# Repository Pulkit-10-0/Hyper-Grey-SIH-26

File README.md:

<h1 align="center">SeaNergy · HyperGrey</h1>
<p align="center"><strong>Sonar that reads the water before it sends the ping.</strong></p>
<p align="center">A low-power, adaptive software-defined sonar transmitter payload for autonomous underwater vehicles.</p>

<p align="center">
  <a href="https://www.hypergrey.in/">Project website</a> ·
  <a href="https://www.youtube.com/playlist?list=PLfZXQHCNRlPQ">Demo playlist</a> ·
  <a href="04-software/releases/SeaNergy-2.2.0___android.apk">Android APK</a> ·
  <a href="07-documentation/research-paper/SeaNergy_Adaptive_Sonar_Research_Paper.pdf">Research paper</a> ·
  <a href="https://www.kaggle.com/code/prakhar1803/adaptive-sonar-waveform-selection">Kaggle notebook</a>
</p>

*The two-DSO bench setup: two digital oscilloscopes, waveform dashboards, controller electronics, probe vessels, and the printed payload housing. September 2026 prototype session.*

SeaNergy is **HyperGrey's Smart India Hackathon 2026** response to **SIH26058**, from the **Ministry of Earth Sciences / National Institute of Ocean Technology**. The problem asks for a low-power, real-time adaptive software-defined sonar transmitter payload for AUVs. Our work connects underwater acoustics, constrained waveform selection, embedded signal generation, analog electronics, mechanical fabrication, and an offline operator console.

The central question is practical: **what pulse should an AUV send next, given the water, the mission, and its energy budget?** SeaNergy makes that decision inspectable—from environmental inputs and propagation assumptions to frequency, bandwidth, pulse duration, waveform, and detection estimates.

## Prototype gallery

A closer look at the physical build, hands-on tuning, and instrumented bench work. Click any photograph to open the original.

| Controller and local displays | Hands-on bench tuning |
|:---:|:---:|
|  |  |
| Four OLEDs, manual controls, sensor wiring, and the breadboard transducer stage. | Adjusting the prototype controls while observing the electrical signals. |

| Two-DSO waveform checks | Burst transmission on the bench |
|:---:|:---:|
|  |  |
| Two oscilloscopes used side by side to inspect electrical waveforms. | Repeated carrier packets separated by quiet intervals. |

### App screens

| Console | Sonar view | Diagnostics |
|:---:|:---:|:---:|
|  |  |  |

*Simulation-mode app screenshots. More environment, waveform, and spectrum views appear in [Operator software](#operator-software). Click a screenshot for its full-resolution view.*

### Graphs dashboard

*September 2026 development dashboard combining serial input readouts with computed waveform, spectral, pulse-compression, propagation, and solver plots. Click to inspect the full-resolution dashboard.*

## Start with the evidence

| Review route | What to open |
|---|---|
| **See the prototype** | [Hardware demo with DSO](https://www.youtube.com/watch?v=S5sL9P1SnnM), [changing water conditions](https://www.youtube.com/watch?v=R3WoJ25fv1Y), and [prototype photographs](08-media/photos/) |
| **Try the interface** | [Android v2.2.0 APK](04-software/releases/SeaNergy-2.2.0___android.apk), [app demo](https://www.youtube.com/watch?v=PedR7m0j_bs), and [software guide](04-software/README.md) |
| **Inspect the engineering** | [Hardware design](01-hardware/README.md), [board verification](01-hardware/verification-summary.md), and [current TX/RX firmware](02-firmware/README.md) |
| **Check the reasoning** | [21-page project research paper](07-documentation/research-paper/SeaNergy_Adaptive_Sonar_Research_Paper.pdf), [literature library](03-research/README.md), and [reproducible modelling package](05-models/) |
| **Review the submission** | [Compliance material](00-submission/compliance-matrix/) and [demo procedure](00-submission/demo-script/demo-script.md) |

**Contents:** [Photo gallery](#prototype-gallery) · [App screens](#app-screens) · [Graphs dashboard](#graphs-dashboard) · [Problem and approach](#problem-and-approach) · [Architecture](#architecture) · [Prototype and hardware](#prototype-and-hardware) · [Firmware](#firmware) · [Research and results](#research-and-results) · [Operator software](#operator-software) · [Verification](#verification-results) · [Reproduce](#reproduce-the-work) · [Team](#team-and-ownership)

## Problem and approach

An AUV carries a finite energy store into water whose acoustic properties change. Higher frequencies can provide finer detail, but propagation loss rises with frequency. A longer pulse carries more energy, but an unmodulated pulse also broadens the return in time. Turbidity introduces further loss and uncertainty; temperature, salinity, depth, and pH affect the propagation model. A fixed waveform therefore commits to one compromise across changing conditions.

SeaNergy explores a transmitter that can adjust that compromise deliberately:

1. **Read the environment.** Use measured inputs where calibrated sensing is available, or explicit simulation inputs during model development.
2. **Estimate propagation.** Calculate sound speed, absorption, scattering loss, and the active-sonar link budget under stated assumptions.
3. **Choose a feasible pulse.** Search a bounded candidate set for useful bandwidth while respecting detection margin and energy constraints.
4. **Generate the waveform.** Prepare a digital pulse, apply its envelope, and let the output peripheral clock the samples.
5. **Inspect the result.** Expose waveform, spectrum, diagnostics, and decision inputs to the operator. The software model also studies echo correlation and feedback.

The intended applications include AUV inspection, survey, and obstacle sensing. SeaNergy brings these ideas into a **bench prototype and engineering development platform**, supported by hardware demonstrations, an operator console, and reproducible research.

## Architecture

The system design brings together environmental sensing, acoustic transmit/receive electronics, embedded processing, and the SeaNergy operator app.

*System design overview showing environmental sensing, acoustic signal paths, embedded processing, mobile connectivity, and session export. Component choices and bench wiring are detailed in the [hardware](01-hardware/README.md) and [TX/RX firmware](02-firmware/README.md) guides. Click the diagram to view it at full resolution.*

| Workstream | Implementation | Delivered artifacts |
|---|---|---|
| **Physical prototype** | Sensor/control electronics, displays, nominal 40 kHz electrical carrier and bursts, printed payload housing | Bench photographs, oscilloscope captures, and demonstration videos |
| **PCB design** | AUV V3 Compact Rev B, 100 × 100 mm, two copper layers, 91 footprints | Checked KiCad project, schematics, BOM, and manufacturing package |
| **Embedded software** | Independent TX synthesis/DMA and RX capture/viewer projects | Source, host waveform tests, cross-build records, and wiring guides |
| **Decision research** | Reproducible 100–500 kHz numerical study with 20,000 generated rows | Dataset, notebook, evaluation metrics, and figures |
| **Operator console** | Offline simulation and telemetry adapters; Android release and iOS source | Android APKs, application source, interface demos, and connection specifications |

## Prototype and hardware

### From bench assembly to a payload form

| Bench integration | Printed payload housing |
|:---:|:---:|
|  |  |
| Prototype electronics, sensor vessels, instrument checks, and operator software in one development setup. | Fabricated housing showing the intended payload form and electronics packaging work. |

| Early prototype integration | Housing fabrication |
|:---:|:---:|
|  |  |
| Sensor connections, local displays, controller electronics, and the breadboard stage during early integration. | The physical printed part and support structure during fabrication. |

The bench assembly made the project tangible: real controllers, analog interfaces, sensor inputs, OLED readouts, transmit/receive elements, and instrumented output. Mechanical work progressed through CAD and 3D printing to physical parts. The [fabrication photo](08-media/readme/SeaNergy-payload-fabrication.jpeg), [fabrication time-lapse](https://www.youtube.com/watch?v=OgWcE8eJ3iM), [STL](01-hardware/enclosure/cad/hyper-grey-v1.stl), and [enclosure documentation](01-hardware/enclosure/) preserve that process.

### Electrical observations

| Nominal 40 kHz carrier | Gated carrier packets |
|:---:|:---:|
|  |  |
| Instrument display: **39.99 kHz**, **25.00 μs**, **3.56 V peak-to-peak**. | Carrier cycles grouped into bursts with gaps between transmissions. |

These September 2026 captures document the prototype's electrical carrier and burst behaviour. The carrier display records **39.99 kHz**, **25.00 μs**, and **3.56 V peak-to-peak**; the burst view shows grouped carrier packets and quiet intervals.

<details>
<summary>Additional oscilloscope observations from the supplied bench session</summary>

| Periodic oscillation | Analog trace with switching transients |
|:---:|:---:|
|  |  |

Additional electrical observations from the September bench session show periodic oscillation, decay, and switching transients. Capture provenance is indexed in the [media guide](08-media/readme/README.md).

</details>

### AUV V3 Compact Rev B PCB

*PCB design render of the checked Rev B manufacturing release.*

The compact interconnect PCB provides wired connections for an **ESP32-S3 main/transmit controller** and a **separate ESP32 receiver**. Controllers and other external modules connect through labelled solder pads and require separate mounting; the 100 × 100 mm dimension describes the interconnect PCB. Its interfaces include two ADS1115 ADCs, DS18B20 temperature sensing, TDS and turbidity channels, four OLED displays, a MAX98357A audio path, and nominal 40 kHz transmit/receive connections. The receive section includes a biased analog gain stage. Main and receive electronics have separate 3.3 V rails with a common ground.

The design spans seven schematic sheets. The [saved verification report](01-hardware/kicad/verification/final-verification.json) records 91 footprints, 483 track segments, six vias, and two ground zones, with **zero ERC violations, zero DRC violations, zero unconnected items, and zero schematic/PCB parity issues**. The saved report provides the design-verification record for this release.

**Inspect or manufacture:** [schematic PDF](01-hardware/schematics/schematic.pdf) · [assembly PDF](01-hardware/kicad/previews/Assembly.pdf) · [Gerber ZIP](01-hardware/pcb/gerbers/AUV_V3_RevB_Compact_Gerbers.zip) · [BOM](01-hardware/bom/) · [release checksums](01-hardware/release-sha256.json) · [wiring and design notes](01-hardware/README.md).

## Firmware

The current firmware uses two independently buildable PlatformIO projects. The implementation separates waveform preparation from peripheral playback so the CPU does not have to write every sample at transmission time.

| Component | Implemented behaviour |
|---|---|
| **ESP32-S3 TX** | Fixed-point carrier phase accumulator and sine lookup table; cached pulse synthesis; complete stereo-buffer preload into I2S DMA; hardware-clocked playback |
| **Waveform modes** | Linear frequency modulation, geometric/logarithmic sweep, and Barker-13 BPSK; Barker uses a fixed midpoint carrier with 13 phase-coded chips |
| **PCM envelopes** | Hann, Blackman, and endpoint-tapered Hamming; mode/window selection and actual sample preview on the displays |
| **Burst scheduling** | GPTimer scheduling and separate GPIO16 PWM gating; no busy-wait sample loop |
| **Control and faults** | Disarmed boot, explicit ARM/STOP, stale-input detection, control heartbeat, playback deadline, missed-period and late-gate faults |
| **ESP32 RX** | GPIO34 ADC capture through I2S DMA, ASCII serial frames, and a Python live waveform/Hann-FFT viewer |

### Output profiles

- **Existing MAX98357A profile:** 48 ksample/s PCM playback with **1–8 kHz** waveform settings. A separate GPIO16 output provides **38–42 kHz rectangular PWM bursts**. The chirp arrays and PCM envelopes apply to I2S, not to that PWM output.
- **Optional PCM5102A profile:** 384 ksample/s PCM for a **38–42 kHz** bench configuration, with documented DAC wiring and a buffered line-level frontend for a suitable power driver.
- **Research profile:** a separate **100–500 kHz numerical study** explores waveform selection and propagation trade-offs.

Five physical potentiometers provide bounded frequency, bandwidth, duration, and amplitude mappings, with sensor voltages and temperature reported separately. Each firmware project includes wiring and bench procedures; [compatibility notes](02-firmware/README.md) map the current five-control TX and earlier three-control board companion.

TX and RX operate as independent bench projects: TX prepares and transmits bursts, while RX captures ADC frames for waveform and FFT inspection. The [earlier ESP-IDF parallel-DAC implementation](02-firmware/legacy/esp-idf-payload/) is preserved as a documented development stage.

**Read the implementation:** [TX guide](02-firmware/tx/README.md) · [TX hardware profiles and bench procedure](02-firmware/tx/HARDWARE.md) · [RX project](02-firmware/rx/) · [architecture](02-firmware/docs/architecture.md).

## Research and results

### Literature that shaped the design

The [research library](03-research/README.md) contains **132 reference PDFs across 15 topic areas**, with topic indexes connecting papers to design decisions. It covers sound speed, absorption, sediment scattering, sonar detection, chirp design, matched filtering, windows and sidelobes, phase codes, cognitive sonar, DDS, transducers, AUV integration, embedded power, and machine learning.

The foundations include Mackenzie's sound-speed relation, Thorp and Francois–Garrison absorption models, active-sonar link budgets, Harris's window analysis, and Barker codes. The [21-page project manuscript](07-documentation/research-paper/SeaNergy_Adaptive_Sonar_Research_Paper.pdf), **“Physics-Constrained Adaptive Sonar Waveform Selection and Low-Power Transmit Architecture for Autonomous Underwater Vehicles,”** brings the modelling, architecture, experiments, and engineering analysis together, with generated studies, team-reported observations, and engineering projections identified within it.

### The decision engine

Each solve evaluates **468 candidates: 13 centre frequencies × 6 bandwidth fractions × 6 pulse durations**. The solver checks the modelled detection margin and energy budget, prioritizes useful feasible bandwidth, and uses energy to distinguish equivalent choices. It includes explicit fallback behaviour when the requested margin cannot be achieved.

The main relationships make the trade-offs visible:

| Relationship | Design implication |
|---|---|
| Range resolution: **ΔR ≈ c / (2B)** | Wider effective bandwidth can separate closer reflectors after compression |
| Pulse-compression gain: **≈ 10 log₁₀(BT)** | A swept pulse can combine pulse energy with a narrower compressed response |
| Two-way propagation loss | A return must survive both outward and return travel; frequency and range matter together |
| Windowing | Lower sidelobes trade against main-lobe width and usable pulse energy |

The notebook uses **Mackenzie + Thorp + parameterized scattering**. The current app implements **Mackenzie + Francois–Garrison**, including depth and pH effects. Each implementation documents its modelling assumptions and calculated resolution.

*Generated numerical study in the 100–500 kHz band, showing selected frequency and calculated resolution under the solver's propagation-loss model.*

### Reproducible dataset

The [dataset](05-models/dataset/adaptive_sonar_waveform_selection.csv) contains **20,000 generated rows and 27 columns**, with seed **20260829**. Its sampling deliberately combines broad coverage with difficult cases:

| Stratum | Rows | Purpose |
|---|---:|---|
| Sweep | 8,000 | Controlled exploration of environmental changes |
| Fill | 5,000 | Broader coverage between selected conditions |
| Scenario | 4,000 | Mission-style combinations of conditions |
| Adversarial | 3,000 | Stress cases outside the requested feasible operating margin |

The generated transmit-side dataset covers **15,399 feasible decisions and 4,601 cases outside the requested margin** under the requested margin, exercising both normal selection and fallback behaviour.

### What the model comparison taught us

We trained three histogram gradient-boosting regressors to imitate the solver's centre frequency, bandwidth, and duration decisions. The routine split contains **12,750 training rows and 4,250 test rows**, with a separate **3,000-row stress set**. The stored [evaluation metrics](05-models/evaluation/metrics.json) report:

| Target | Constant mean baseline MAE | Surrogate MAE | Reduction |
|---|---:|---:|---:|
| Centre frequency | 69.57 kHz | 3.58 kHz | 94.8% |
| Bandwidth | 61.30 kHz | 4.00 kHz | 93.5% |
| Pulse duration | 2.404 ms | 1.666 ms | 30.7% |

The comparison supports retaining the bounded solver as the decision reference. The evaluation uses pre-decision environmental and reference-band features following a leakage audit. On the recorded **development-host benchmark**, the precomputed solver's median was **40.3 μs**, compared with **7.45 ms** for single-row Python surrogate inference.

A separate **synthetic residual-correction study** evaluates learning propagation-model error. Its gradient-boosting correction achieved **0.729 dB MAE**, compared with **1.005 dB** for a linear turbidity model and **1.963 dB** for a constant correction.

**Explore:** [notebook and figures](05-models/notebook/) · [evaluation methods and results](05-models/evaluation/) · [Kaggle version](https://www.kaggle.com/code/prakhar1803/adaptive-sonar-waveform-selection) · [dataset checks](05-models/qa.py).

## Operator software

The console turns the physics and signal-processing work into an interface that can be demonstrated without a network connection. It runs the numerical work on the device and labels **Simulation** and **Telemetry** modes explicitly.

| Environment | Waveform | Spectrum |
|:---:|:---:|:---:|
|  |  |  |

*App screenshots in simulation mode. Frequencies, compression, echo, resolution, and power values in this mode are numerical outputs.*

The current source provides **11 tabs plus a Scenario screen**, with individual ping detail. Together they cover the console, sonar PPI, waveform, spectrum, echo/correlation, environment, mission, power, diagnostics, logs, settings, and scenarios.

| Capability | Implementation |
|---|---|
| **Environmental reasoning** | Temperature, salinity, turbidity, depth, and pH inputs; sound-speed and absorption breakdown |
| **Waveform inspection** | CW, LFM, geometric sweeps, Barker-13; rectangular, Hann, Hamming, and Blackman windows |
| **Signal processing** | FFT, spectrogram, transmit replica, modelled echo, and matched-filter analysis in simulation |
| **Operator workflow** | Mission parameters, diagnostics, last 200 ping records in memory, and local CSV export |
| **Android links** | Native USB CDC-ACM/CP210x and BLE adapters; Wi-Fi WebSocket with HTTP fallback |
| **iOS source** | Shared application source, native Xcode project, and Wi-Fi connection path |

The console includes a documented telemetry contract for environmental readings and pulse settings. Its simulation engine, connection adapters, and the standalone RX waveform viewer are described in the [software guide](04-software/README.md) and [firmware architecture](02-firmware/docs/architecture.md).

**Stack:** React Native **0.86.2**, Expo **57**, React **19**, TypeScript, Skia charts, and a Kotlin Android connection module. The [static project website](04-software/website/) uses HTML, CSS, and JavaScript and can run locally without a backend.

**Install or inspect:** [universal Android APK](04-software/releases/SeaNergy-2.2.0___android.apk) · [smaller architecture-specific APKs](04-software/releases/) · [release record](04-software/releases/BUILDS.md) · [Android source](04-software/mobile-android/) · [iOS source](04-software/mobile-ios/) · [software guide](04-software/README.md).

## Demonstration library

The [Hyper Grey SIH 2026 (SeaNergy) playlist](https://www.youtube.com/playlist?list=PLfZXQHCNRlPQ) contains six videos, verified on **16 October 2026**:

| Video | Duration |
|---|---:|
| [1.1 Hardware Demo (with DSO)](https://www.youtube.com/watch?v=S5sL9P1SnnM) | 1:17 |
| [1.2 Hardware Demo ( Changing Water Conditions )](https://www.youtube.com/watch?v=R3WoJ25fv1Y) | 1:54 |
| [2.1 android app demo](https://www.youtube.com/watch?v=PedR7m0j_bs) | 4:43 |
| [3.1 Hardware parts description](https://www.youtube.com/watch?v=1TF7gd7LjTs) | 3:51 |
| [3.2 Hardware Graphs: Overview and Approach](https://www.youtube.com/watch?v=NZ1CEJT-cyo) | 3:23 |
| [Custom Payload Fabrication Time-Lapse](https://www.youtube.com/watch?v=OgWcE8eJ3iM) | 0:09 |

Additional material: [Google Drive photo collection](https://drive.google.com/drive/folders/15Eb-qjRcj5WRZOpzTAzsjD7BbMPWwIrb?usp=sharing) · [repository photo archive](08-media/photos/) · [media provenance and captions](08-media/readme/README.md).

## Verification results

Completed checks cover PCB consistency, embedded waveform generation, application behaviour, and reproducible modelling.

| Evidence | Recorded result | What it establishes |
|---|---|---|
| **Bench photographs and scope captures** | Physical assembly, displayed nominal 40 kHz carrier, and burst packets | Earlier prototype construction and electrical observations |
| **Rev B KiCad checks** | ERC/DRC/unconnected/parity all zero | Design consistency and routing checks for the saved board revision |
| **Current TX host waveform tests** | **409,765 checks passed**, strict C++17 build with undefined-behaviour sanitizer | Analytic waveform agreement, window/mode combinations, bounds, endpoints, amplitude and stereo behaviour |
| **Current TX cross-build record** | Existing, headless, and PCM5102A profiles passed on 16 October 2026 | Source compilation across the three pinned hardware profiles |
| **Android release record** | **106 core assertions and 33 render tests**, with TypeScript checks recorded for v2.2.0 | Core logic, rendered screens, and release-time type checks |
| **Research artifacts** | Generated dataset, notebook, metrics, figures, and QA script | Reproducible numerical work under the documented models |
| **Validation dossier** | Test plans, procedures, and labelled engineering projections | Requirements traceability, acceptance criteria, and test documentation |

The [validation folder](06-validation/), [firmware measurement notes](02-firmware/measurements/README.md), [board report](01-hardware/verification-summary.md), and [software build record](04-software/releases/BUILDS.md) provide procedures, conditions, and supporting records.

## Reproduce the work

### Firmware builds

Install PlatformIO, then run these commands from the repository root. The optional DAC profile compiles independently but requires its documented hardware before use.

```sh
pio run -d 02-firmware/tx -e esp32s3_existing
pio run -d 02-firmware/tx -e esp32s3_headless
pio run -d 02-firmware/tx -e esp32s3_pcm5102a
pio run -d 02-firmware/rx -e esp32dev
```

Run the portable waveform checks with a C++17 compiler:

```sh
cd 02-firmware/tx
c++ -std=c++17 -O1 -Wall -Wextra -Werror -pedantic \
  -fsanitize=undefined -Iinclude src/waveform.cpp tests/waveform_test.cpp \
  -o /tmp/seanergy-waveform-test
/tmp/seanergy-waveform-test
```

For wiring, serial commands, fault handling, and bench measurements, start with the [firmware guide](02-firmware/README.md).

### Research notebook and evaluation

Use **Python 3.12** in a virtual environment. Starting at the repository root:

```sh
cd 05-models/notebook
python -m pip install -r requirements.txt
python run_local.py
cd ../evaluation
python evaluate.py
cd ..
python qa.py
```

These scripts regenerate numerical artifacts and compare the solver/model studies. The existing QA hash check is sensitive to CSV line endings: macOS/Linux LF output can differ from the recorded Windows CRLF hash even when the data content is identical. Resolve that formatting difference before interpreting a stale-hash report as a data mismatch. Read the [notebook guide](05-models/notebook/README.md) and [evaluation notes](05-models/evaluation/) for assumptions and expected outputs.

### Android application

Starting at the repository root, use **Node.js 22** to install the locked dependencies and run the checks:

```sh
cd 04-software/mobile-android
npm ci
npm run check
npm start
```

The development server requires an installed matching native development build. Use the [release APK](04-software/releases/SeaNergy-2.2.0___android.apk) to review the packaged Android app. See the [software documentation](04-software/README.md) for native builds and platform requirements.

### Local website

Starting at the repository root:

```sh
python3 -m http.server 8000 --directory 04-software/website
```

Open [http://localhost:8000](http://localhost:8000). The static [index.html](04-software/website/index.html) also supports direct offline viewing.

## Engineering effort and repository map

Each project and component folder includes a local README with purpose, entry points, and status. Android resource directories and iOS asset catalogs are mapped in their native parent guides so their format-specific contents remain valid.

The work spans a literature library, a deterministic data generator, numerical DSP, model comparisons, two embedded controllers, analog and PCB design, enclosure fabrication, native mobile connections, an operator interface, and submission evidence. The repository preserves both results and decisions so a reviewer can trace how an idea became a part, a waveform, a screen, or a test.

| Folder | Contents |
|---|---|
| [00-submission](00-submission/) | Compliance matrix, demo script, equipment and recovery checklists |
| [01-hardware](01-hardware/) | Schematic, KiCad board, BOM, Gerbers, analog design, enclosure CAD and manufacturing notes |
| [02-firmware](02-firmware/) | Current TX/RX projects, wiring and build guidance, measurements, and archived ESP-IDF work |
| [03-research](03-research/README.md) | 15 topic indexes and 132 reference PDFs |
| [04-software](04-software/) | Android/iOS source, operator console, website, connection adapters, and APK releases |
| [05-models](05-models/) | Generated dataset, notebook, figures, constrained solver, surrogate and residual-model evaluation |
| [06-validation](06-validation/) | Test procedures, planned measurements, and evidence dossier |
| [07-documentation](07-documentation/) | Research manuscript, technical report, protocols, and operating guidance |
| [08-media](08-media/) | Prototype photographs, app screenshots, design imagery, and README media |
| [09-business](09-business/) | Cost assumptions, market study, deployment roadmap, and IP material |
| [10-project](10-project/) | Team responsibilities, build history, decisions, readiness, and risks |

The [build log](10-project/timeline/build-log.md), [decision record](10-project/timeline/decisions.md), and [ownership handoffs](10-project/team/ownership.md) give further context. Dated cost and market estimates are collected in the [business material](09-business/README.md).

## Team and ownership

**HyperGrey · Team 138620 · Maharaja Surajmal Institute of Technology**

| Member | Documented responsibility |
|---|---|
| **Pulkit** | Team lead; acoustic/physics model, firmware, and PCB design |
| **Aarushi** | Presentation, documentation, business analysis, and IP work |
| **Harshada** | Analog electronics, power, and transducer drive |
| **Ananya** | Mechanical integration, tank layout, and safety |
| **Prakhar** | Mobile application, telemetry, and offline operator interface |
| **Jaspreet** | Dataset, notebook/model evaluation, and demonstration QA |

[Team record](10-project/team/team.md) · [Subsystem ownership](10-project/team/ownership.md) · [Project website](https://www.hypergrey.in/)

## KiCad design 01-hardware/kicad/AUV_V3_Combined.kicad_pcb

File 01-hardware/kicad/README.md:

# AUV V3 combined PCB — Compact Revision B

This is one **100 × 100 mm, two-layer PCB** for the ESP32-S3 main/TX controller, classic ESP32 DevKit receiver, two ADS1115 modules, four OLED displays, DS18B20, TDS/turbidity modules, three potentiometers, MAX98357A audio module, speaker and ultrasonic TX/RX elements.

**The original board already used two layers.** Revision B reduces its outline by placing the components and solder pads closer together and routing the copper again. It retains all 91 board references, the same circuit and external connections. The packaged firmware is a historical board companion; current TX/RX compatibility is described below.

| | Revision A | Compact Revision B |
| --- | --- | --- |
| Board size | 200 × 150 mm | 100 × 100 mm |
| Board area | 30,000 mm² | 10,000 mm² — 66.7% smaller |
| Copper layers | 2 | 2 |
| Connections | Labelled plated solder pads | Same functional pad connections |
| Existing modules | Wired externally | Wired externally |

The AUV V3 revision A in this comparison is the preceding two-layer layout recorded in [compact_equivalence.json](verification/compact_equivalence.json). It is distinct from the [archived 100 × 80 mm, four-layer preliminary concept](../rev-a-preliminary/README.md).

The larger first layout provided generous spacing for hand assembly and labels. The compact board fits those same connections into a smaller area. The existing controllers and modules still connect by wires to labelled plated solder pads; secure those external modules separately. The **100 × 100 mm size applies to this PCB**, not to the complete collection of ESP32 boards, displays, sensors and their wiring.

## Open and use

1. Clone or download this repository and keep this entire `kicad/` folder intact. Keep its `libraries/` and `3dmodels/` folders alongside the project.
2. Open **AUV_V3_Combined.kicad_pro** in **KiCad 9.0.7 or later**. Use its schematic and PCB editors to inspect or edit the design.
3. Read **docs/Assembly_and_Wiring.md** or its printable HTML version before fitting parts or connecting modules. Each solder pad, component and test point is listed there.
4. Use **docs/BOM_purchase.csv** to purchase board components. Existing modules are listed separately. Most parts are through-hole; Q2, U3 and F1 are surface-mount. Match the specified body dimensions because the layout is compact.
5. Use the final [AUV_V3_RevB_Compact_Gerbers.zip](AUV_V3_RevB_Compact_Gerbers.zip) for bare-board manufacture, together with [fabrication/Manufacturing_Notes.md](fabrication/Manufacturing_Notes.md). Use revision B files throughout; do not mix revision A copper or drill files with revision B.

The native schematics, PCB, project settings, local symbol library, footprint libraries and referenced 3D models are included. Standard KiCad library licensing and provenance are preserved in the libraries folder. The 3D preview uses generic package models; DIP sockets may be drawn without the inserted IC bodies.

## Circuit and firmware

- The two controllers retain **separate MAIN3V3 and RX3V3 supplies**, with a shared ground. Power each ESP32 through its own USB. External regulated 5 V powers TX, audio and optionally the sensor modules.
- TX uses the IRLZ44N, an **AO3400A level translator and TC4426AEPA gate driver**. The two inversions retain GPIO HIGH = transmitter ON. A 1 kΩ resistor across the piezo provides its discharge/reset path.
- Sensor inputs accept the documented **0–5 V output range** through 2:1 dividers, filtering, TMUX1511 powered-off isolation and MCP100 supply supervision. Series 1 kΩ resistors limit brief ADC-input transient current.
- The supplied [firmware/ESP32-S3](firmware/ESP32-S3/README.md) is the historical companion snapshot. Its TDS/turbidity voltage calculations compensate for the 2:1 dividers; its three potentiometer calculations and TX polarity retain the prior board assumptions. The [packaging record](firmware/README.md) documents that divider patch.
- Current [TX](../../02-firmware/tx/) and [RX](../../02-firmware/rx/) projects are maintained separately. The imported TX expects five potentiometers and reports ADS1115 node voltages without the companion divider compensation. Read the [compatibility notes](../../02-firmware/docs/architecture.md) before connecting it to this board; their serial diagnostics and capture formats are documented in those projects.
- RX preserves the MCP6002 reference follower and nominal gain-23 amplifier. A 100 Ω resistor separates its output from GPIO34. Its finite bandwidth and physical wiring affect the measured 40 kHz response.

## Completed design checks

**The compact revision B passes the final checks:** zero ERC violations, zero DRC violations, zero unconnected items and zero schematic/PCB parity differences, with no DRC exclusions. All 91 footprints and 236 physical pins, including 3 intentionally unconnected pins, agree with the design. The board contains 483 routed track segments, 6 vias and 2 ground-plane zones across its two copper layers. All 56 model references resolve to packaged local 3D files. The seven-page schematic PDF carries revision B on every sheet. Fourteen fabrication files were exported from the checked PCB; the supplied verification reports and SHA-256 hashes identify the release.

The prototype design release includes checks for connectivity, geometric clearances, schematic/PCB consistency, packaged model paths and export provenance.

J17 pad 3 connects directly to the GND plane and may require a little extra heating time during soldering; the assembly guide explains the connection.

The requested 100 × 100 mm outline is used. Use M3 mounting screw heads and washers no larger than 7 mm outside diameter; oversized washers could approach J5. Allow additional enclosure space for mounted component height, wire bends and the separately secured external modules. Before connecting modules, confirm their functional pin labels and supply requirements, and check the ESP32-S3 regulator's current budget. Sensor supply selectors initially have no shunts; select 3.3 V or 5 V only after checking the actual module. The assembly guide contains staged first-power and waveform checks.

## Included review files

- **AUV_V3_Combined_Schematic.pdf** — native schematic export.
- **previews/Assembly.pdf** — top-view assembly drawing; print at 100% and verify its scale before using it as a physical template.
- **previews/Board_3D.png** — package and placement preview.
- **previews/Front_Copper.svg** and **Back_Copper.svg** — copper views.
- **verification/** — revision B electrical, PCB and consistency checks, and export hashes.
- **docs/** — assembly guide, complete pin tables, BOM and existing-module list.
- **firmware/** — the existing source copy, exact patch and original-source hashes.

After any circuit or layout change, update both the schematic and PCB as needed, refill copper zones, rerun ERC/DRC with schematic parity, then regenerate fabrication outputs. Do not reuse older Gerbers after changing the board.

## Folder guides

[Project documentation](docs/README.md) · [Fabrication](fabrication/README.md) · [Previews](previews/README.md) · [Verification](verification/README.md) · [Standard footprints](libraries/README.md) · [Wire-pad footprints](AUV_WirePads.pretty/README.md) · [3D models](3dmodels/README.md) · [Historical firmware](firmware/README.md) · [Backups](AUV_V3_Combined-backups/README.md)

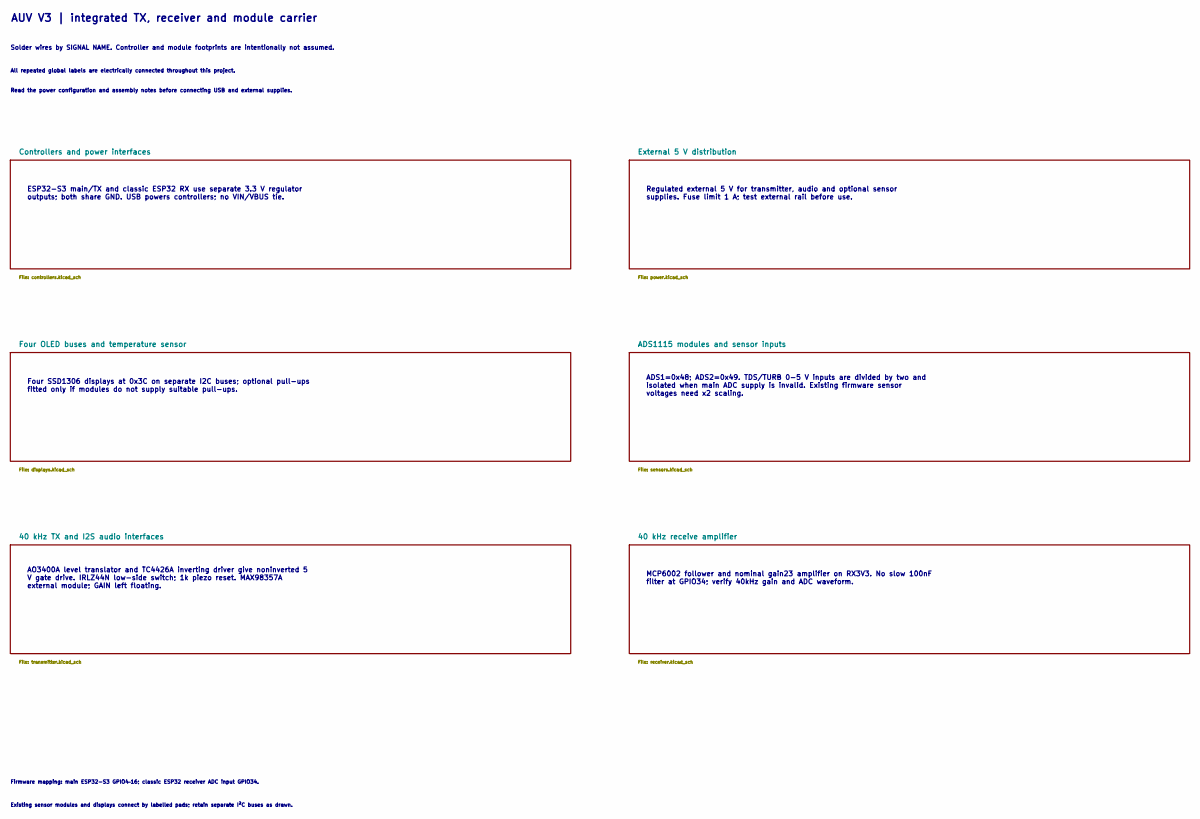
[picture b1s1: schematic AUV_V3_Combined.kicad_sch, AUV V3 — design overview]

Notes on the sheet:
AUV V3 | integrated TX, receiver and module carrier
Solder wires by SIGNAL NAME. Controller and module footprints are intentionally not assumed.
All repeated global labels are electrically connected throughout this project.
Read the power configuration and assembly notes before connecting USB and external supplies.
ESP32-S3 main/TX and classic ESP32 RX use separate 3.3 V regulator outputs; both share GND. USB powers controllers; no VIN/VBUS tie.
Regulated external 5 V for transmitter, audio and optional sensor supplies. Fuse limit 1 A; test external rail before use.
Four SSD1306 displays at 0x3C on separate I2C buses; optional pull-ups fitted only if modules do not supply suitable pull-ups.
ADS1=0x48; ADS2=0x49. TDS/TURB 0-5 V inputs are divided by two and isolated when main ADC supply is invalid. Existing firmware sensor voltages need x2 scaling.
AO3400A level translator and TC4426A inverting driver give noninverted 5 V gate drive. IRLZ44N low-side switch; 1k piezo reset. MAX98357A external module; GAIN left floating.
MCP6002 follower and nominal gain23 amplifier on RX3V3. No slow 100nF filter at GPIO34; verify 40kHz gain and ADC waveform.
Firmware mapping: main ESP32-S3 GPIO4–16; classic ESP32 receiver ADC input GPIO34.
Existing sensor modules and displays connect by labelled pads; retain separate I²C buses as drawn.

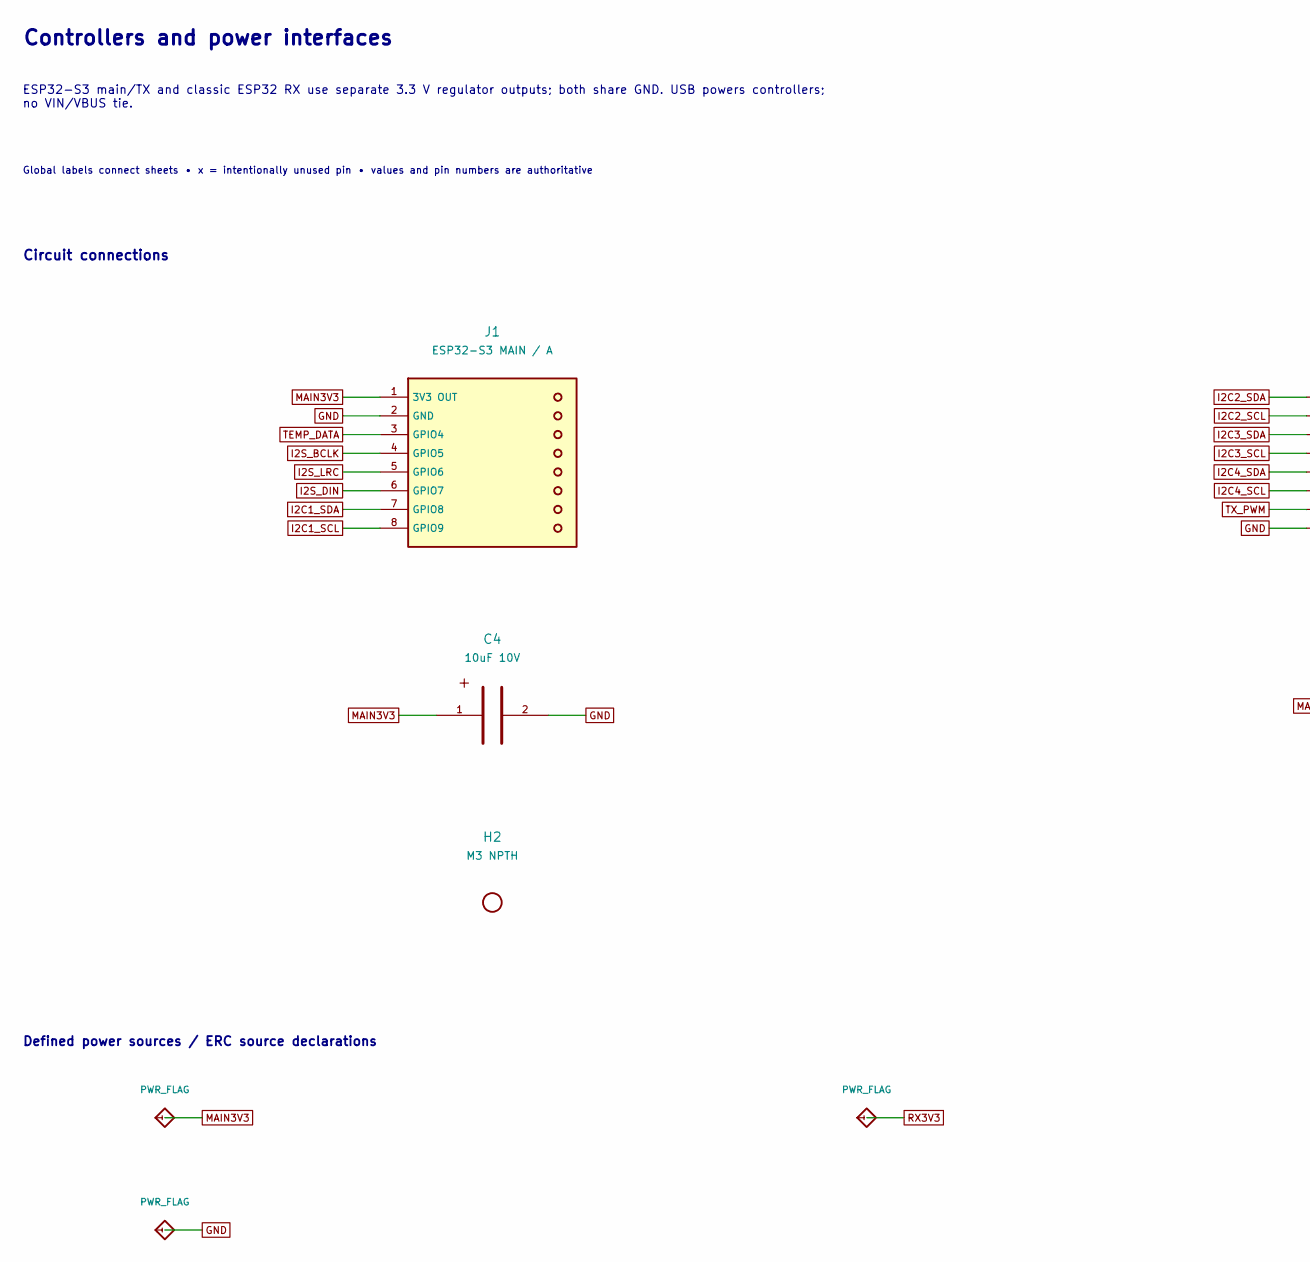
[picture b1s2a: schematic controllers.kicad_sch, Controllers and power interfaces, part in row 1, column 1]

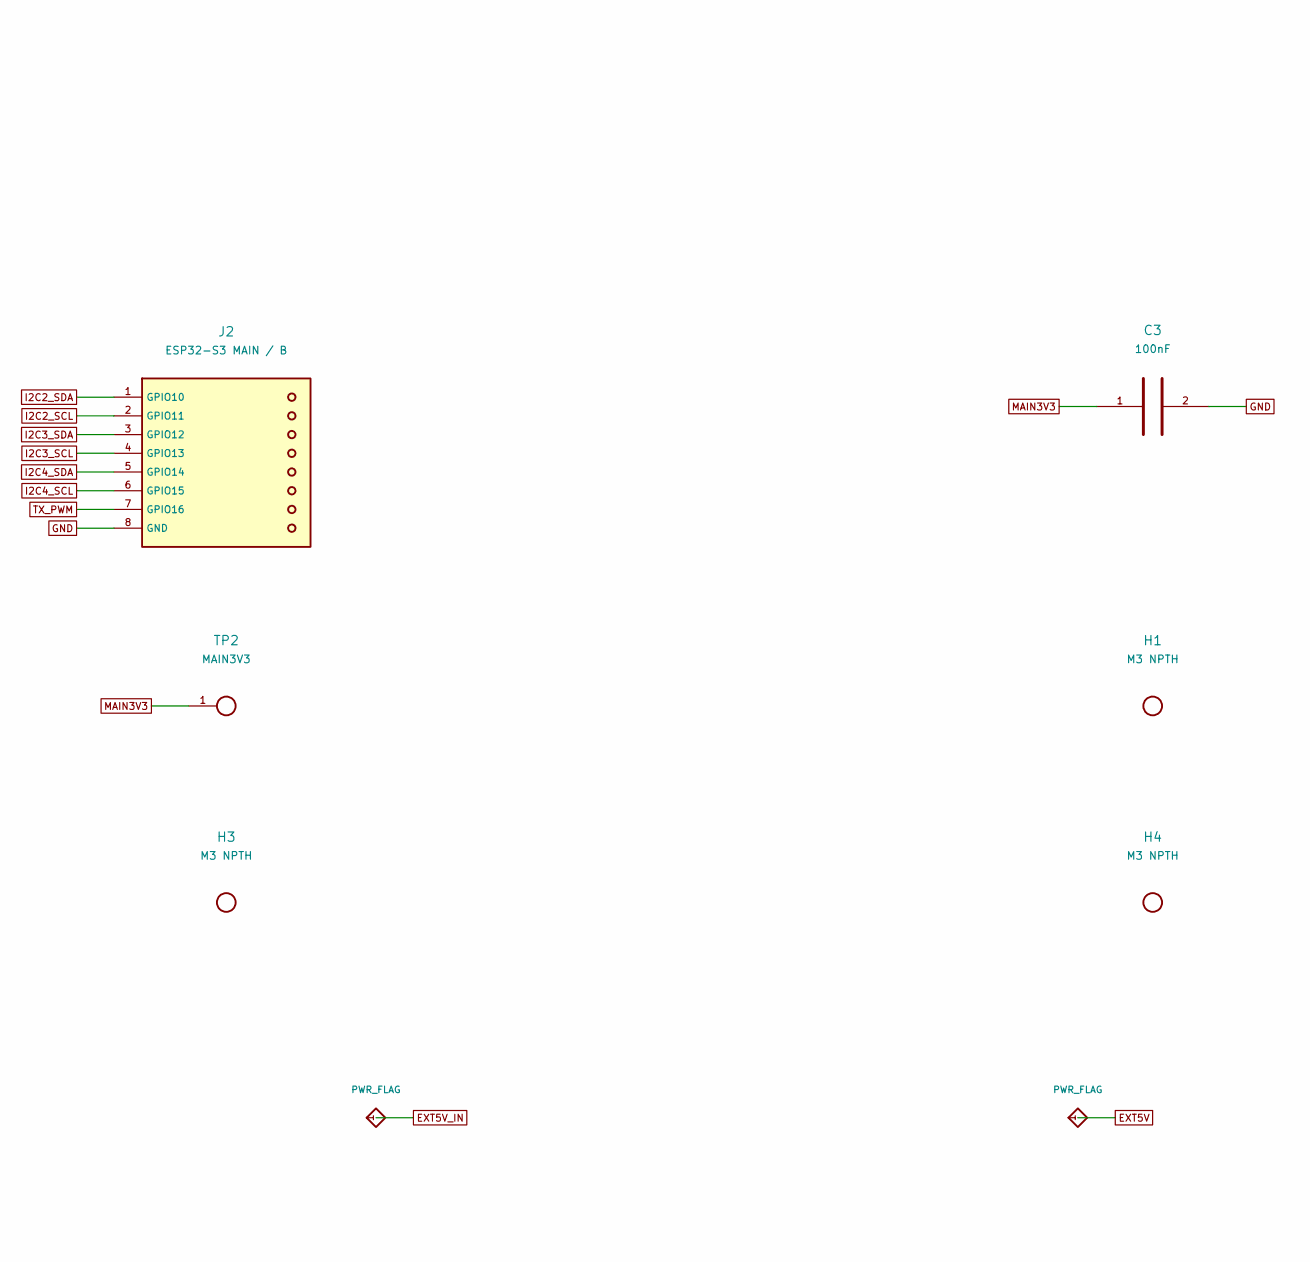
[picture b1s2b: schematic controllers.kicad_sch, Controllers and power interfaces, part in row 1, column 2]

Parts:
C3: 100nF; C_Disc_D3.0mm_W1.6mm_P2.50mm
C4: 10uF 10V; CP_Radial_D5.0mm_P2.00mm
H1, H2, H3, H4: M3 NPTH; MountingHole_3.2mm_M3
J1: ESP32-S3 MAIN / A; WirePads_1x08; MPN Bare plated through-hole wiring pads
J2: ESP32-S3 MAIN / B; WirePads_1x08; MPN Bare plated through-hole wiring pads
TP2: MAIN3V3; TestPoint_THTPad_D2.0mm_Drill1.0mm

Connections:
GND: C3.2, C4.2, J1.2 (GND), J2.8 (GND); also elsewhere on the board
I2C1_SCL: J1.8 (GPIO9); also elsewhere on the board
I2C1_SDA: J1.7 (GPIO8); also elsewhere on the board
I2C2_SCL: J2.2 (GPIO11); also elsewhere on the board
I2C2_SDA: J2.1 (GPIO10); also elsewhere on the board
I2C3_SCL: J2.4 (GPIO13); also elsewhere on the board
I2C3_SDA: J2.3 (GPIO12); also elsewhere on the board
I2C4_SCL: J2.6 (GPIO15); also elsewhere on the board
I2C4_SDA: J2.5 (GPIO14); also elsewhere on the board
I2S_BCLK: J1.4 (GPIO5); also elsewhere on the board
I2S_DIN: J1.6 (GPIO7); also elsewhere on the board
I2S_LRC: J1.5 (GPIO6); also elsewhere on the board
MAIN3V3: C3.1, C4.1, J1.1 (3V3 OUT), TP2.1; also elsewhere on the board
TEMP_DATA: J1.3 (GPIO4); also elsewhere on the board
TX_PWM: J2.7 (GPIO16); also elsewhere on the board

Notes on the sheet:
Controllers and power interfaces
ESP32-S3 main/TX and classic ESP32 RX use separate 3.3 V regulator outputs; both share GND. USB powers controllers; no VIN/VBUS tie.
Global labels connect sheets • x = intentionally unused pin • values and pin numbers are authoritative
Circuit connections
Defined power sources / ERC source declarations

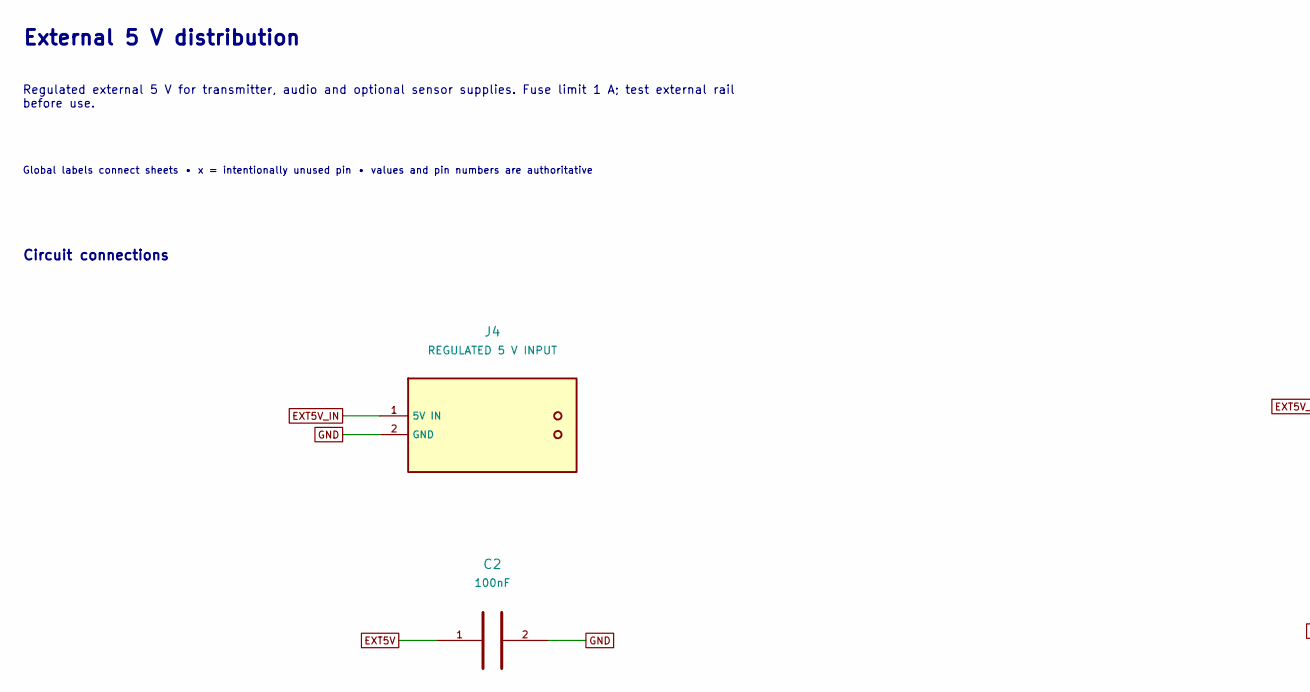
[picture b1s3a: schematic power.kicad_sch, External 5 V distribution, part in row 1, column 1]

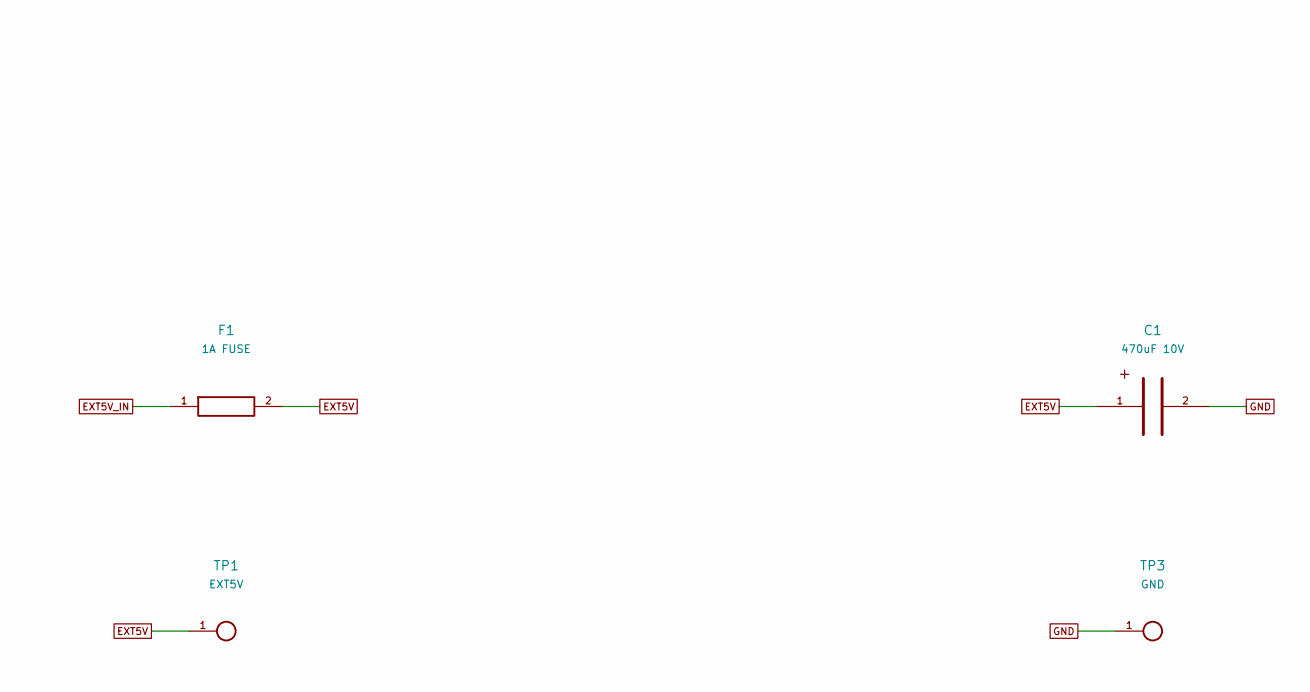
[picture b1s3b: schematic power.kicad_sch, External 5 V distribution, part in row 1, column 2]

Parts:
C1: 470uF 10V; CP_Radial_D8.0mm_P3.50mm; MPN 470 uF >=10 V, diameter <=8 mm, pitch 3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
C2: 100nF; C_Disc_D3.0mm_W1.6mm_P2.50mm
F1: 1A FUSE; Fuse_1206_3216Metric; MPN Littelfuse 0466001.NR
J4: REGULATED 5 V INPUT; WirePads_1x02; MPN Bare plated through-hole wiring pads
TP1: EXT5V; TestPoint_THTPad_D2.0mm_Drill1.0mm
TP3: GND; TestPoint_THTPad_D2.0mm_Drill1.0mm

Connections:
EXT5V: C1.1, C2.1, F1.2, TP1.1; also elsewhere on the board
EXT5V_IN: F1.1, J4.1 (5V IN)
GND: C1.2, C2.2, J4.2 (GND), TP3.1; also elsewhere on the board

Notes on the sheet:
External 5 V distribution
Regulated external 5 V for transmitter, audio and optional sensor supplies. Fuse limit 1 A; test external rail before use.
Global labels connect sheets • x = intentionally unused pin • values and pin numbers are authoritative
Circuit connections

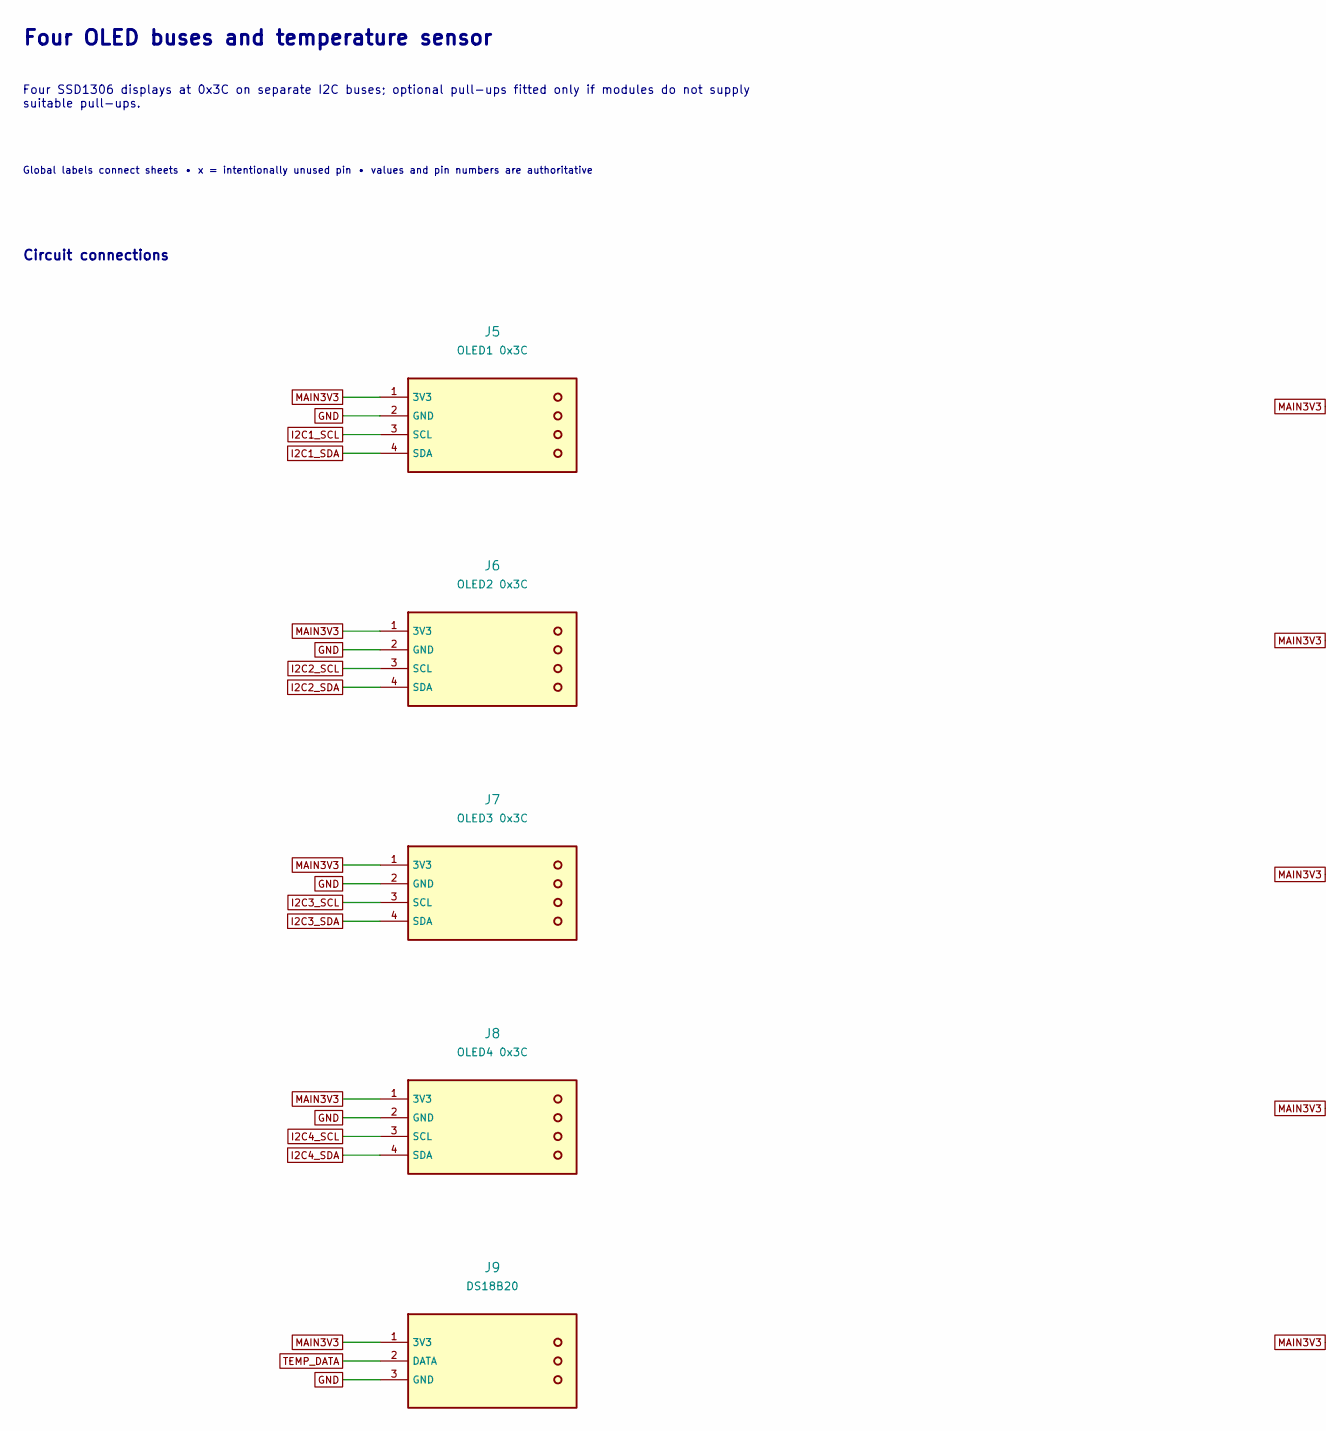
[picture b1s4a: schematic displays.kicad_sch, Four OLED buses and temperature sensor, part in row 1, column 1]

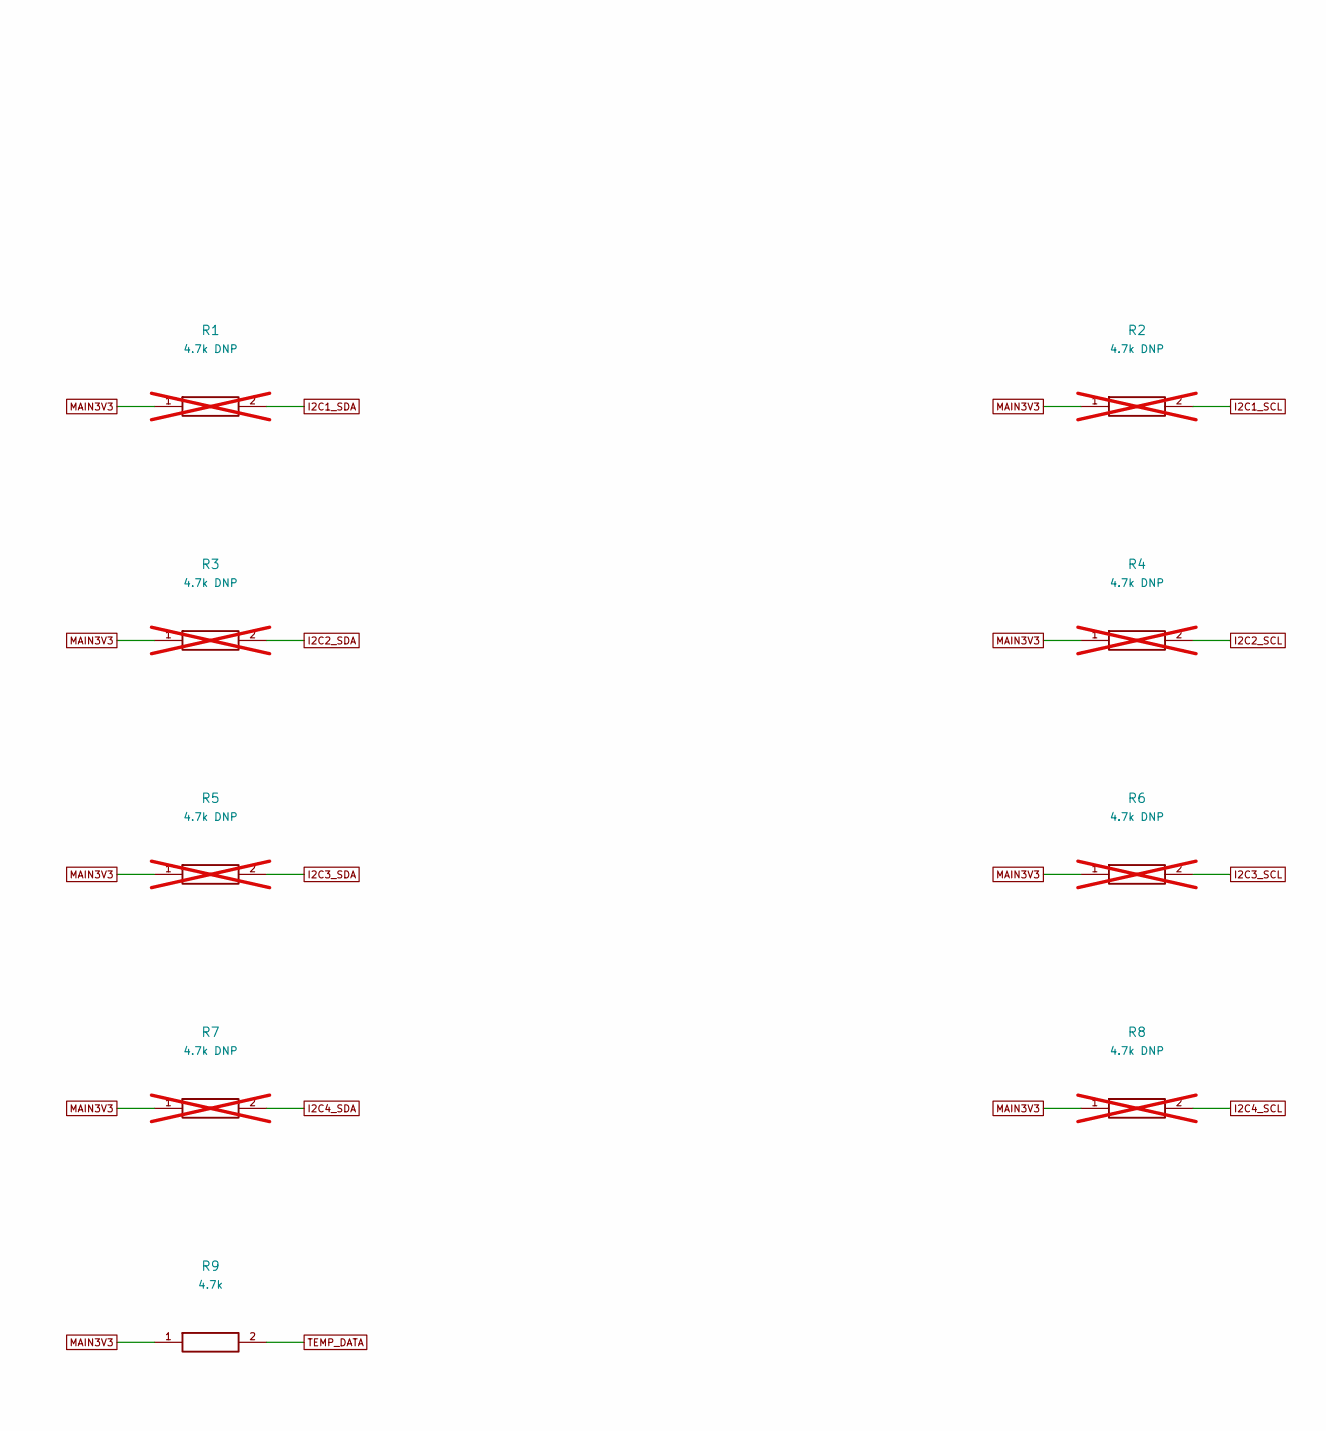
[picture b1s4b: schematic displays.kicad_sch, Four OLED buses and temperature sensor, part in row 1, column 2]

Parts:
J5: OLED1 0x3C; WirePads_1x04; MPN Bare plated through-hole wiring pads
J6: OLED2 0x3C; WirePads_1x04; MPN Bare plated through-hole wiring pads
J7: OLED3 0x3C; WirePads_1x04; MPN Bare plated through-hole wiring pads
J8: OLED4 0x3C; WirePads_1x04; MPN Bare plated through-hole wiring pads
J9: DS18B20; WirePads_1x03; MPN Bare plated through-hole wiring pads
R1, R2, R3, R4, R5, R6, R7, R8: 4.7k DNP; R_Axial_DIN0207_L6.3mm_D2.5mm_P7.62mm_Horizontal; not fitted
R9: 4.7k; R_Axial_DIN0207_L6.3mm_D2.5mm_P7.62mm_Horizontal

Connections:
GND: J5.2 (GND), J6.2 (GND), J7.2 (GND), J8.2 (GND), J9.3 (GND); also elsewhere on the board
I2C1_SCL: J5.3 (SCL), R2.2; also elsewhere on the board
I2C1_SDA: J5.4 (SDA), R1.2; also elsewhere on the board
I2C2_SCL: J6.3 (SCL), R4.2; also elsewhere on the board
I2C2_SDA: J6.4 (SDA), R3.2; also elsewhere on the board
I2C3_SCL: J7.3 (SCL), R6.2; also elsewhere on the board
I2C3_SDA: J7.4 (SDA), R5.2; also elsewhere on the board
I2C4_SCL: J8.3 (SCL), R8.2; also elsewhere on the board
I2C4_SDA: J8.4 (SDA), R7.2; also elsewhere on the board
MAIN3V3: J5.1 (3V3), J6.1 (3V3), J7.1 (3V3), J8.1 (3V3), J9.1 (3V3), R1.1, R2.1, R3.1, R4.1, R5.1, R6.1, R7.1, R8.1, R9.1; also elsewhere on the board
TEMP_DATA: J9.2 (DATA), R9.2; also elsewhere on the board

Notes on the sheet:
Four OLED buses and temperature sensor
Four SSD1306 displays at 0x3C on separate I2C buses; optional pull-ups fitted only if modules do not supply suitable pull-ups.
Global labels connect sheets • x = intentionally unused pin • values and pin numbers are authoritative
Circuit connections
